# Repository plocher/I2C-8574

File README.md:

# I2C-8574
## License: CERN Open Hardware Licence v1.2

I2C PCF8474-based IO Expander with 4x IO4 connections

### Introduction

This board was originally produced to help me build control panels for
my model railroad - I needed to connect many different buttons, switches
and lights to an Arduino, and also connect the Arduino to a
communications bus (Ethernet, CAN or Loconet), and I couldn\'t find
anything that had both high IO point density AND visual feedback.

I started with a simple Arduino
[ShowMeShield](/pages/ShowMeShield "wikilink") with Active-Low monitoring LEDs on each pin.
I quickly iterated (understatement) through at least a dozen designs, trying to
discern what worked well and what didn\'t.  I\'ll spare you the details...
I was aiming to support up to the max I2C devices that can be used together; 
for the PCF8474 series, that would be 8x devices of each type, for a total of 16x8, or 128 i/o points.

(Active-LOW means that the LOGICAL "ON" state is when the PHYSICAL state is low.
In this case, the indication LED is on when the desired pin is grounded; 
when programming, writing a \"1\" to an Active Low port will cause it to ground).

### Cautions

With several hundred IO loads, and up to 32 external breakout devices, a
suitable power supply needs to be used.

In practice, a 2A 9-12VDC supply a good choice.

This supply needs to power the Arduino, its direct IO loads, the I2C
expander chain AND provide \~100mA to each IO4 device. Instead of
relying on the Arduino\'s onboard regulated supply (which is only good
for about 100mA itself), each board has its own regulator, and there is
a common supply feed that can handle about 2.5A @ 12v. If more power is
needed, the daisy chained power feed thru can be replaced with a
per-board independent supply.

### Specifications

This IO board is based on the 8574 I2C 8-bit IO Expander, with a
buffered LED driver (discrete P-FETs) connected to a
bank of LEDs that show the status of the I/O lines in real time.

Each board provides a latched set of 16x IO points, with each point
being software selectable to be either an input or an output. The
individual points are reasonably protected from the environment, and can
easily drive or sink 10 mA each. By using active low inputs and outputs, the
effects of environmental noise are reduced - remote sensors only need to
ground an I/O point to register activity.

#### Communication Protocol {#communication_protocol}

``` {.cpp}
Simple I2C Reads and Writes:
int I2Cextender::read8(int i2caddr) {
    int _data = -1;
    Wire.requestFrom(i2caddr, 1);
    if(Wire.available()) {
      _data = Wire.receive();
    }
    return _data;
}

void I2Cextender::write8(int i2caddr, int data)
{ 
    Wire.beginTransmission(i2caddr);
    Wire.send(0xff & data);
    Wire.endTransmission();  
}
```

See [I2Cexpander](https://github.com/plocher/I2Cexpander) for a more complete interface library.

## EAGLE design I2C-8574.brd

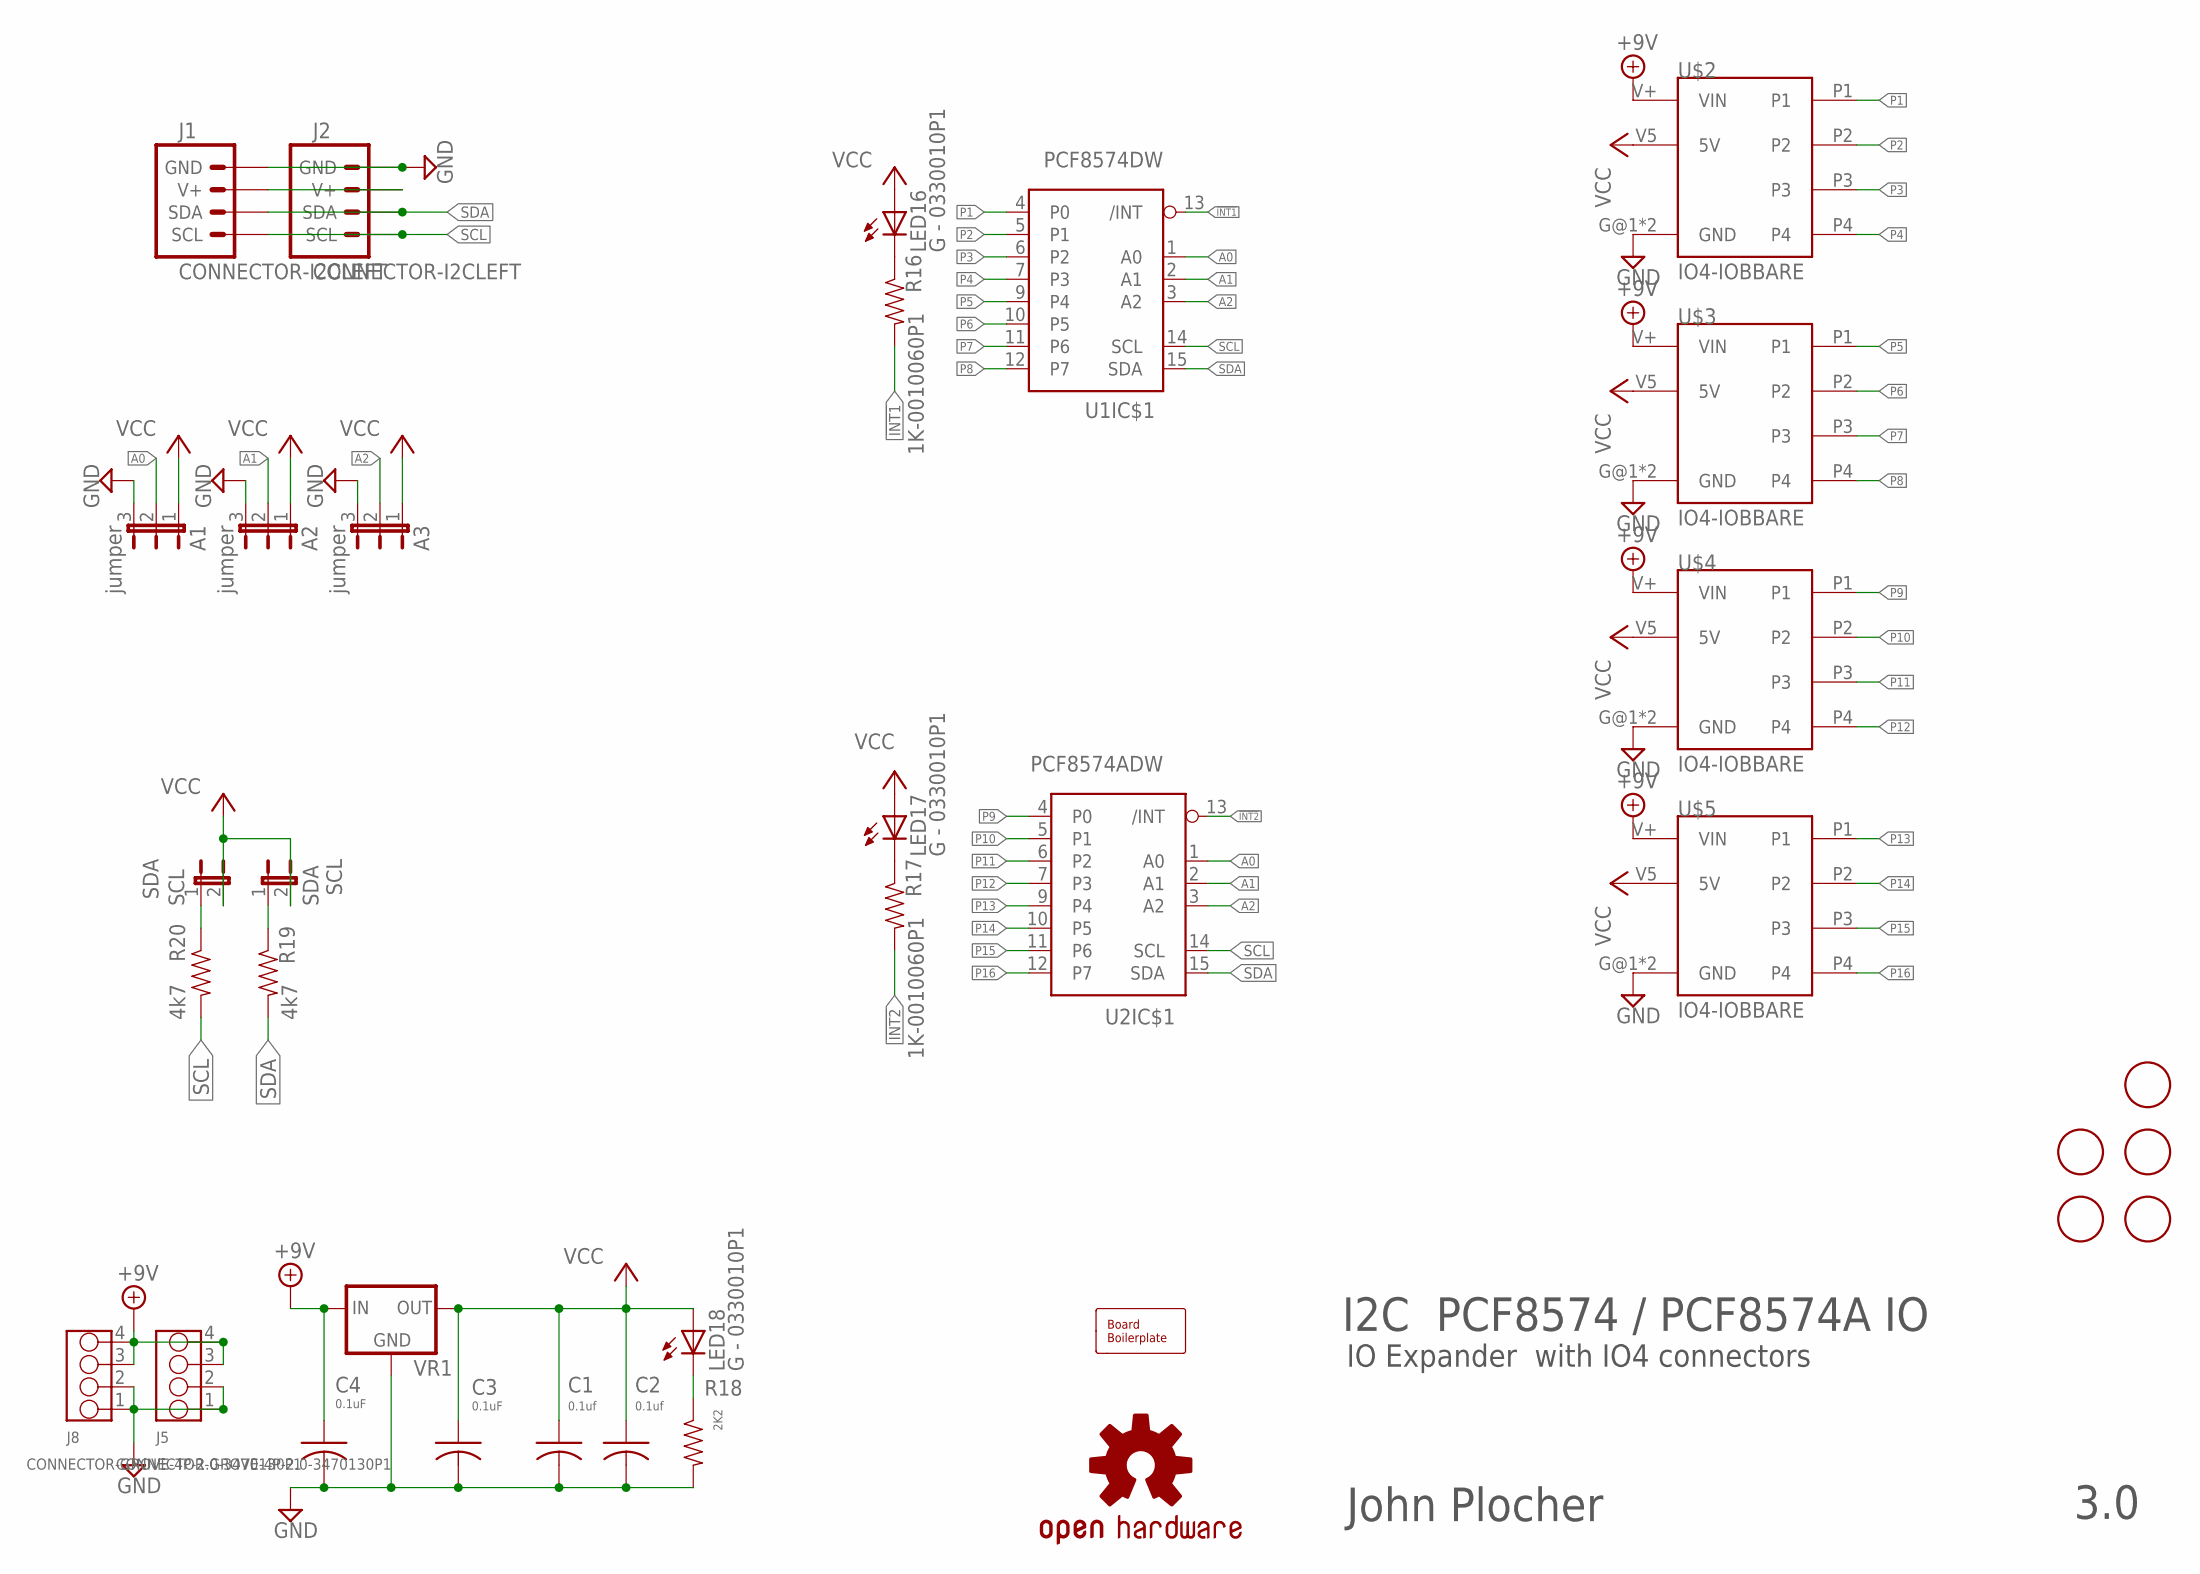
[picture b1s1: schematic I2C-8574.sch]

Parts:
A1, A2, A3: jumper; 1X03
BOARD1: BOARD80X100-NOHOLES; BOARD-DINRAIL-3.17IN-NOHOLES
C1, C2: 0.1uf; 0805-CAP
C3, C4: 0.1uF; 0805-CAP
FID1, FID2, FID3: FIDUCIAL; FIDUCIAL_1MM
FID-U1, FID-U2: FIDUCIAL; FIDUCIAL_1MM
J1, J2: CONNECTOR-I2CLEFT; I2C-L
J5, J8: CONNECTOR-GROVE-4P-2.0-3470130P1; 4P-2.0
LED16, LED17, LED18: G - 0330010P1; 0603-LED
R16, R17: 1K-0010060P1; 0805-RES
R18: 2K2; 0805-RES
R19, R20: 4k7; 0805-RES
SCL: SDA; 1X02_LOCK
SDA: SCL; 1X02_LOCK
U1: PCF8574DW; SO-16DW
U2: PCF8574ADW; SO-16DW
U$1: OSHW-LOGOL; OSHW-LOGO-L
U$2, U$3, U$4, U$5: IO4-IOBBARE; IO4-IOB
VR1: VREG-DPAK-5; TO-252

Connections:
!INT1: R16.2, U1.13 (/INT)
!INT2: R17.2, U2.13 (/INT)
+9V: C4.1, J5.3, J5.4, J8.3, J8.4, U$2.V+ (VIN), U$3.V+ (VIN), U$4.V+ (VIN), U$5.V+ (VIN), VR1.1 (IN)
A0: A1.2, U1.1 (A0), U2.1 (A0)
A1: A2.2, U1.2 (A1), U2.2 (A1)
A2: A3.2, U1.3 (A2), U2.3 (A2)
GND: A1.3, A2.3, A3.3, C1.2, C2.2, C3.2, C4.2, J1.GND, J1.GND@1 (GND), J2.GND, J2.GND@1 (GND), J5.1, J5.2, J8.1, J8.2, R18.2, U1.8 (GND), U2.8 (GND), U$2.G@1 (GND), U$2.G@2 (GND), U$3.G@1 (GND), U$3.G@2 (GND), U$4.G@1 (GND), U$4.G@2 (GND), U$5.G@1 (GND), U$5.G@2 (GND), VR1.2 (GND)
unnamed: LED18.C, R18.1
unnamed: R19.1, SCL.1
unnamed: R20.1, SDA.1
unnamed: LED17.C, R17.1
unnamed: LED16.C, R16.1
unnamed: J1.V+, J1.V+@1 (V+), J2.V+, J2.V+@1 (V+)
P1: U1.4 (P0), U$2.P1
P2: U1.5 (P1), U$2.P2
P3: U1.6 (P2), U$2.P3
P4: U1.7 (P3), U$2.P4
P5: U1.9 (P4), U$3.P1
P6: U1.10 (P5), U$3.P2
P7: U1.11 (P6), U$3.P3
P8: U1.12 (P7), U$3.P4
P9: U2.4 (P0), U$4.P1
P10: U2.5 (P1), U$4.P2
P11: U2.6 (P2), U$4.P3
P12: U2.7 (P3), U$4.P4
P13: U2.9 (P4), U$5.P1
P14: U2.10 (P5), U$5.P2
P15: U2.11 (P6), U$5.P3
P16: U2.12 (P7), U$5.P4
SCL: J1.SCL, J1.SCL@1 (SCL), J2.SCL, J2.SCL@1 (SCL), R20.2, U1.14 (SCL), U2.14 (SCL)
SDA: J1.SDA, J1.SDA@1 (SDA), J2.SDA, J2.SDA@1 (SDA), R19.2, U1.15 (SDA), U2.15 (SDA)
VCC: A1.1, A2.1, A3.1, C1.1, C2.1, C3.1, LED16.A, LED17.A, LED18.A, SCL.2, SDA.2, U1.16 (VCC), U2.16 (VCC), U$2.V5 (5V), U$3.V5 (5V), U$4.V5 (5V), U$5.V5 (5V), VR1.3 (OUT)

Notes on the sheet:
I2C PCF8574 / PCF8574A IO
IO Expander with IO4 connectors
John Plocher
3.0

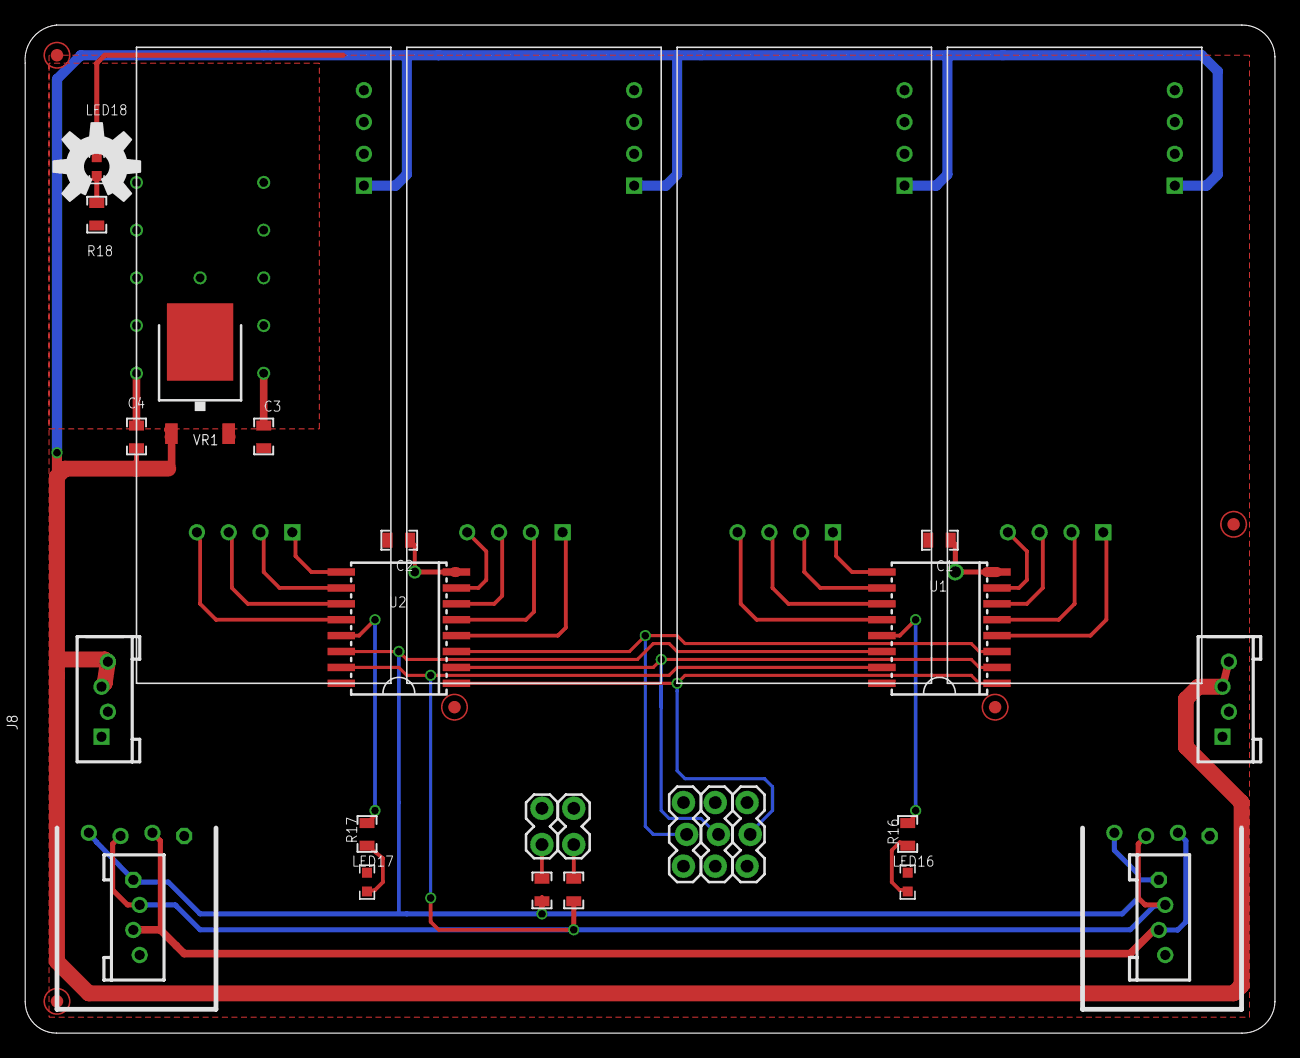
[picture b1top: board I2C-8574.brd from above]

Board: 2 copper layers, 99.8 x 80.5 mm, 35 parts (0 on the bottom side), 32 nets.

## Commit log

2019-12-09 added graphic
